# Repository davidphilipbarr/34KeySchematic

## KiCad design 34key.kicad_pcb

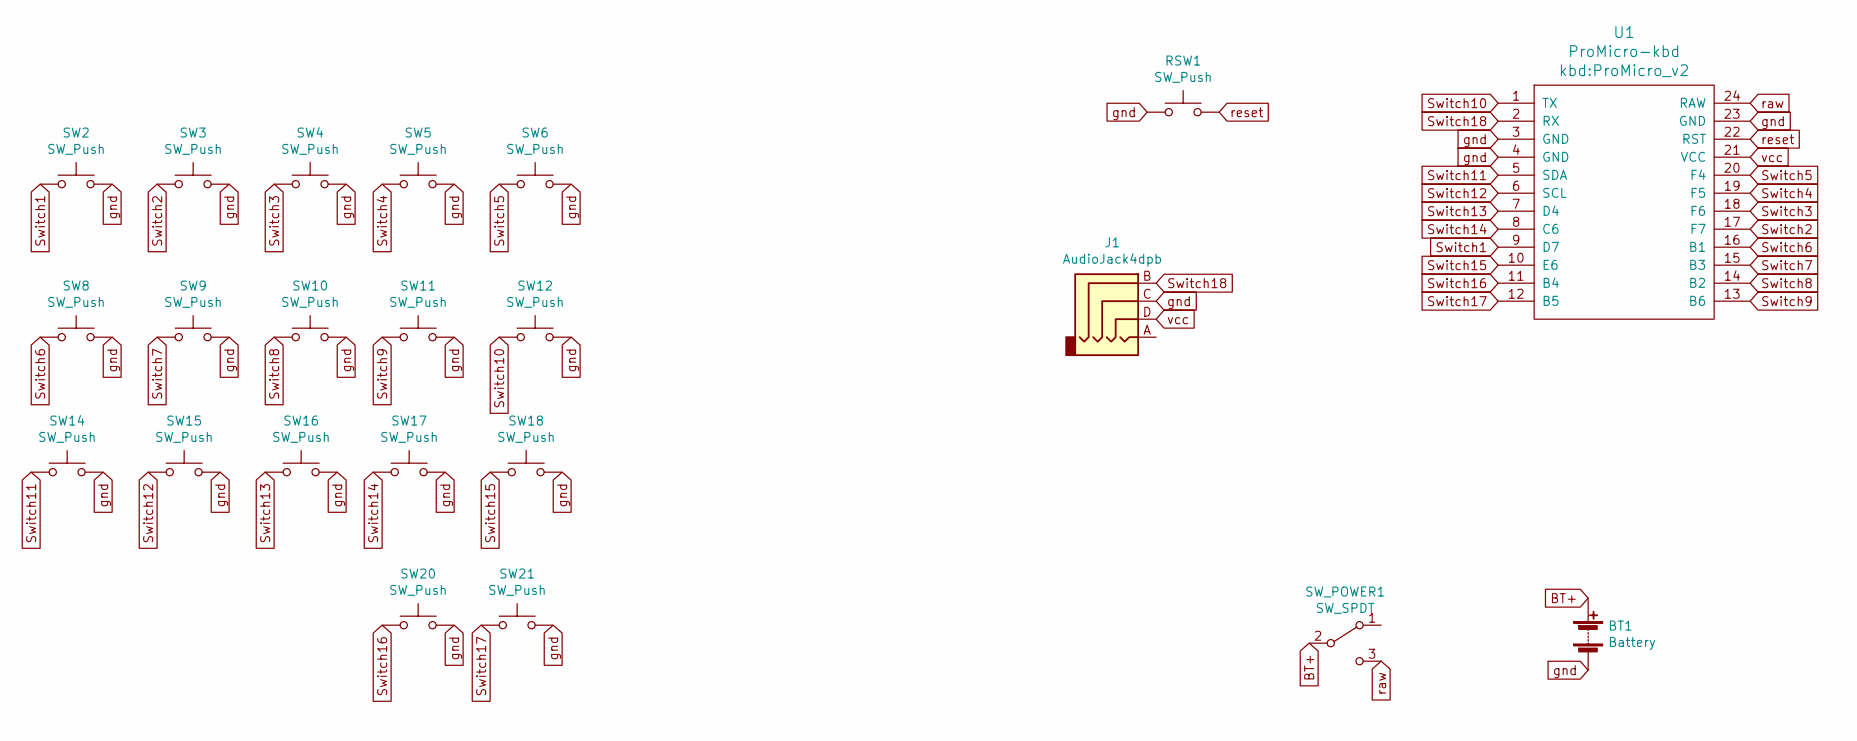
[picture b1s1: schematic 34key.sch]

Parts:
BT1: Battery; BatteryHolder_Keystone_2998_1x6.8mm
J1: AudioJack4dpb; MJ-4PP-9
RSW1: SW_Push; ResetSW
SW2, SW3, SW4, SW5, SW6, SW8, SW9, SW10, SW11, SW12, SW14, SW15, SW16, SW17, SW18, SW20, SW21: SW_Push; SW_PG1350_rev_DPB
SW_POWER1: SW_SPDT; SPDT_C128955
U1: ProMicro-kbd; ProMicro_v2

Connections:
BT+: BT1.1 (+), SW_POWER1.2 (B); also elsewhere on the board
Switch1: SW2.1, U1.9 (D7)
Switch2: SW3.1, U1.17 (F7)
Switch3: SW4.1, U1.18 (F6)
Switch4: SW5.1, U1.19 (F5)
Switch5: SW6.1, U1.20 (F4)
Switch6: SW8.1, U1.16 (B1)
Switch7: SW9.1, U1.15 (B3)
Switch8: SW10.1, U1.14 (B2)
Switch9: SW11.1, U1.13 (B6)
Switch10: SW12.1, U1.1 (TX)
Switch11: SW14.1, U1.5 (SDA)
Switch12: SW15.1, U1.6 (SCL)
Switch13: SW16.1, U1.7 (D4)
Switch14: SW17.1, U1.8 (C6)
Switch15: SW18.1, U1.10 (E6)
Switch16: SW20.1, U1.11 (B4)
Switch17: SW21.1, U1.12 (B5)
Switch18: J1.B, U1.2 (RX)
gnd: BT1.2 (-), J1.C, RSW1.1, SW2.2, SW3.2, SW4.2, SW5.2, SW6.2, SW8.2, SW9.2, SW10.2, SW11.2, SW12.2, SW14.2, SW15.2, SW16.2, SW17.2, SW18.2, SW20.2, SW21.2, U1.3 (GND), U1.4 (GND), U1.23 (GND); also elsewhere on the board
raw: SW_POWER1.3 (C), U1.24 (RAW)
reset: RSW1.2, U1.22 (RST)
vcc: J1.D, U1.21 (VCC)

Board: 2 copper layers, 23 parts (0 on the bottom side), 23 nets, no tracks yet.

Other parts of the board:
Bat+1: MountingHole_Pad; 1pin_conn
BatGND1: MountingHole_Pad; 1pin_conn

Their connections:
BT+: Bat+1.1; also elsewhere on the board
gnd: BatGND1.1; also elsewhere on the board
